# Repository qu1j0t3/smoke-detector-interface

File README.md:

# smoke-detector-interface
Interface board for Amphenol Telaire SM-UART-04L laser dust sensor, with some random other functions

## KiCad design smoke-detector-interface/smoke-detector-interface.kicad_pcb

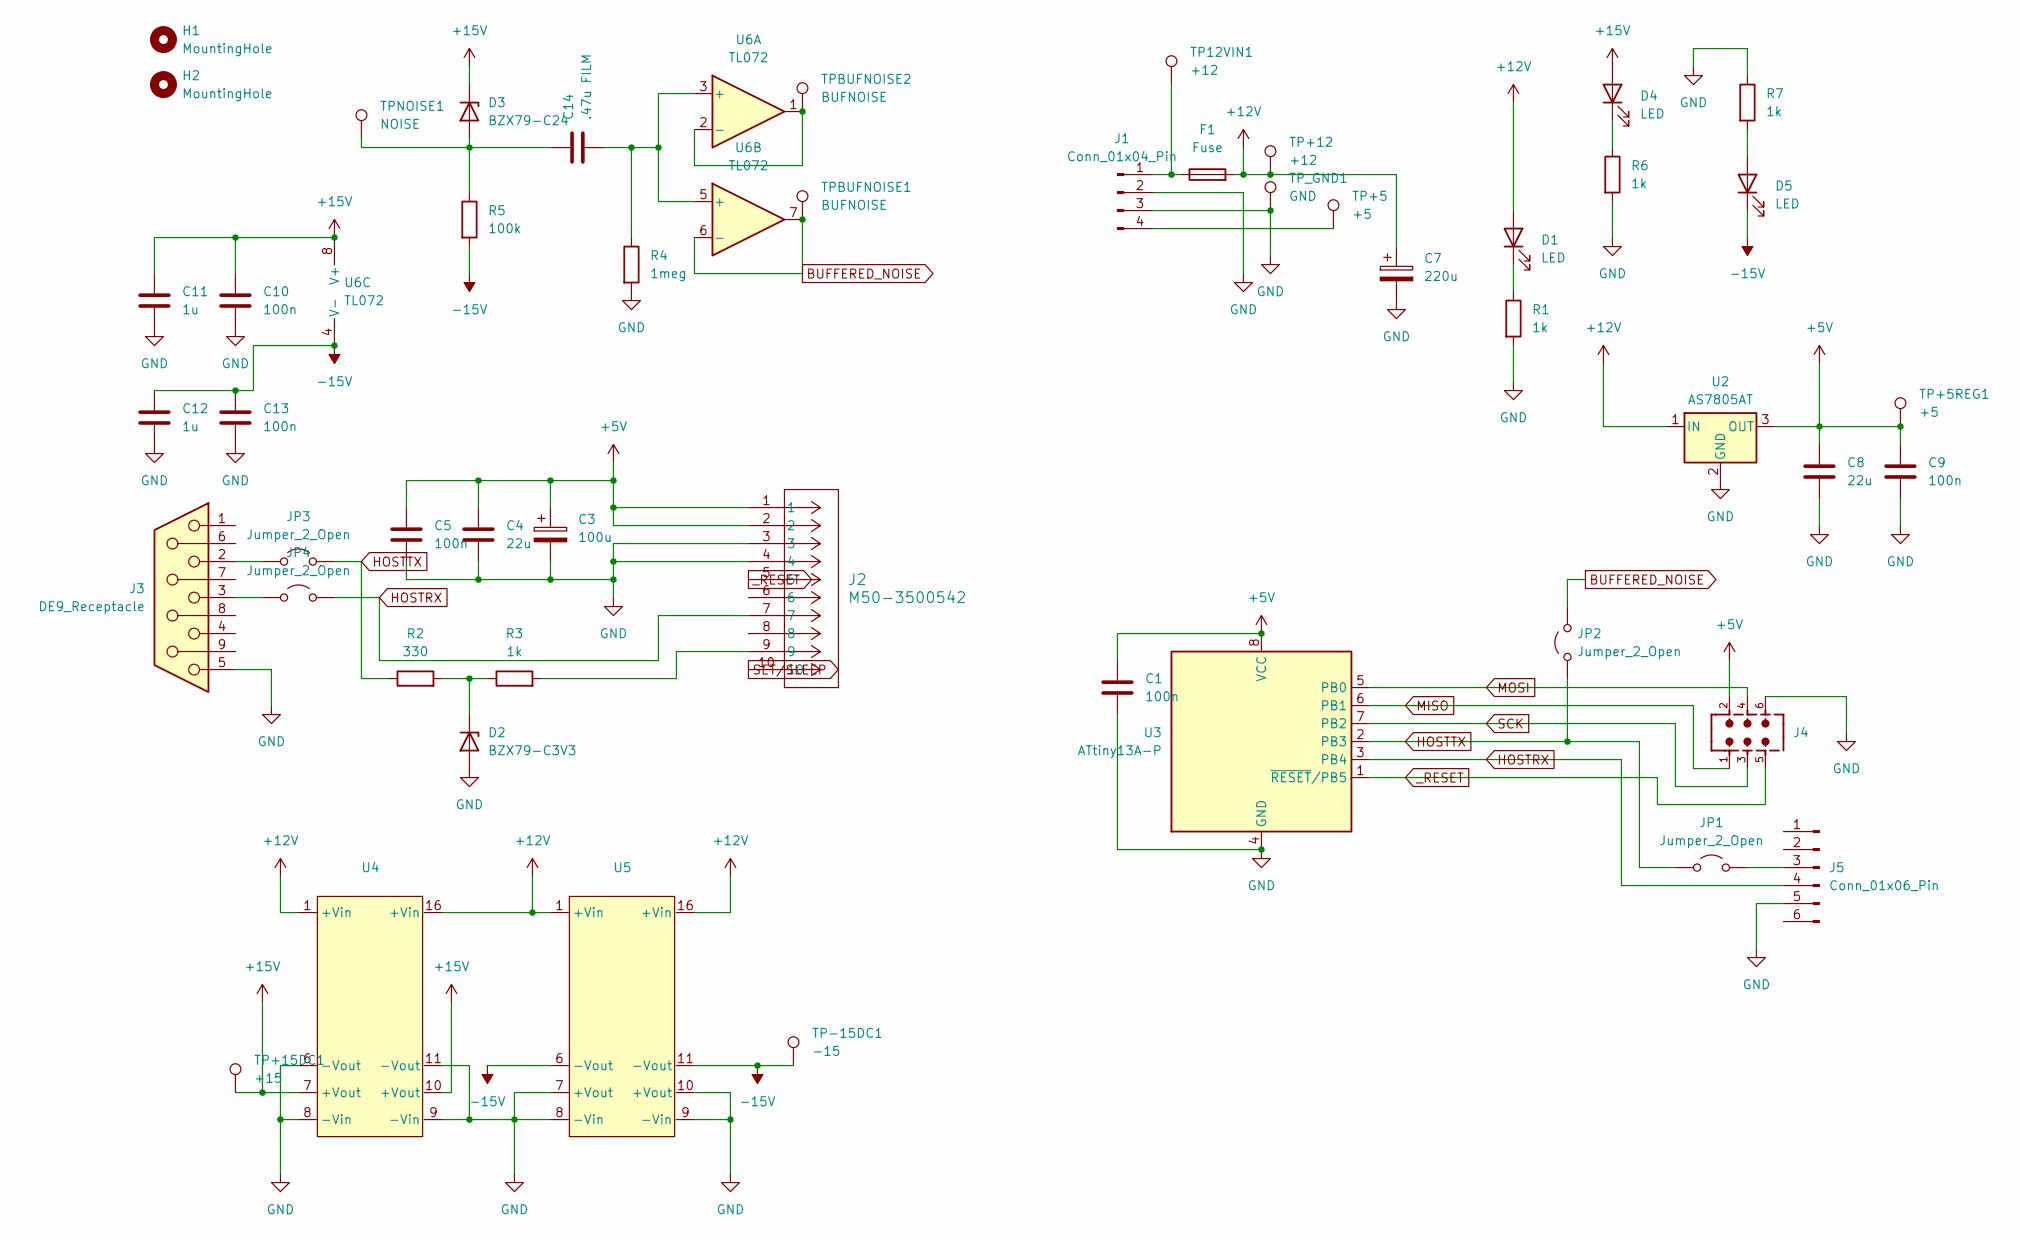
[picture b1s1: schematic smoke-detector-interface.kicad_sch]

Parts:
C1, C5, C9, C10, C13: 100n; C_Disc_D4.3mm_W1.9mm_P5.00mm
C3: 100u; CP_Radial_D6.3mm_P2.50mm
C4, C8: 22u; CP_Radial_D5.0mm_P2.00mm
C7: 220u; CP_Axial_L18.0mm_D8.0mm_P25.00mm_Horizontal
C11, C12: 1u; C_Disc_D3.8mm_W2.6mm_P2.50mm
C14: .47u FILM; C_Rect_L7.2mm_W3.5mm_P5.00mm_FKS2_FKP2_MKS2_MKP2
D1, D4, D5: LED; LED_D5.0mm
D2: BZX79-C3V3; D_DO-35_SOD27_P7.62mm_Horizontal
D3: BZX79-C24; D_DO-35_SOD27_P12.70mm_Horizontal
F1: Fuse; 01530008
H1, H2: MountingHole; MountingHole_3.2mm_M3
J1: Conn_01x04_Pin; 641737-1_TYC
J2: M50-3500542; CONN10_500542_HRW
J3: DE9_Receptacle; LD09S13A4GX00LF_AMP
J4: 61200621621; PART-NUMBER 61200621621
J5: Conn_01x06_Pin; PinHeader_1x06_P2.54mm_Vertical
JP1, JP2, JP3, JP4: Jumper_2_Open; R_Axial_DIN0204_L3.6mm_D1.6mm_P7.62mm_Horizontal
R1, R3, R6, R7: 1k; R_Axial_DIN0207_L6.3mm_D2.5mm_P10.16mm_Horizontal
R2: 330; R_Axial_DIN0207_L6.3mm_D2.5mm_P10.16mm_Horizontal
R4: 1meg; R_Axial_DIN0207_L6.3mm_D2.5mm_P10.16mm_Horizontal
R5: 100k; R_Axial_DIN0207_L6.3mm_D2.5mm_P10.16mm_Horizontal
TP12VIN1: +12; TestPoint_THTPad_2.5x2.5mm_Drill1.2mm
TP+5, TP+5REG1: +5; TestPoint_THTPad_2.5x2.5mm_Drill1.2mm
TP+12: +12; TestPoint_THTPad_2.5x2.5mm_Drill1.2mm
TP+15DC1: +15; TestPoint_THTPad_2.5x2.5mm_Drill1.2mm
TP-15DC1: -15; TestPoint_THTPad_2.5x2.5mm_Drill1.2mm
TPBUFNOISE1, TPBUFNOISE2: BUFNOISE; TestPoint_THTPad_2.5x2.5mm_Drill1.2mm
TPNOISE1: NOISE; TestPoint_THTPad_2.5x2.5mm_Drill1.2mm
TP_GND1: GND; TestPoint_THTPad_2.5x2.5mm_Drill1.2mm
U2: AS7805AT; TO-220-3_Vertical
U3: ATtiny13A-P; DIP-8_W7.62mm_Socket
U4, U5: DIP-16_W7.62mm_Socket
U6: TL072; DIP-8_W7.62mm_Socket

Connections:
+5V: C1.1, C3.1, C4.1, C5.1, C8.1, C9.1, J2.1, J2.2, J4.2, TP+5REG1.1, U2.3 (OUT), U3.8 (VCC)
+12V: C7.1, D1.2 (A), F1.2, TP+12.1, U2.1 (IN), U4.1 (+Vin), U4.16 (+Vin), U5.1 (+Vin), U5.16 (+Vin)
+15V: C10.1, C11.1, D3.1 (K), D4.2 (A), TP+15DC1.1, U4.7 (+Vout), U4.10 (+Vout), U6.8 (V+)
-15V: C12.1, C13.1, D5.1 (K), R5.2, TP-15DC1.1, U5.6 (-Vout), U5.11 (-Vout), U6.4 (V-)
BUFFERED_NOISE: JP2.2 (B), TPBUFNOISE1.1, U6.6 (-), U6.7
GND: C1.2, C3.2, C4.2, C5.2, C7.2, C8.2, C9.2, C10.2, C11.2, C12.2, C13.2, D2.2 (A), J1.2, J1.3, J2.3, J2.4, J3.5, J4.6, J5.5, R1.2, R4.2, R6.2, R7.1, TP_GND1.1, U2.2 (GND), U3.4 (GND), U4.6 (-Vout), U4.8 (-Vin), U4.9 (-Vin), U4.11 (-Vout), U5.7 (+Vout), U5.8 (-Vin), U5.9 (-Vin), U5.10 (+Vout)
HOSTRX: J2.7, J5.4, JP4.2 (B), U3.3 (PB4)
HOSTTX: JP1.1 (A), JP2.1 (A), JP3.2 (B), R2.1, U3.2 (PB3)
MISO: J4.1, U3.6 (PB1)
MOSI: J4.4, U3.5 (PB0)
unnamed: D1.1 (K), R1.1
unnamed: D2.1 (K), R2.2, R3.1
unnamed: C14.1, D3.2 (A), R5.1, TPNOISE1.1
unnamed: D4.1 (K), R6.1
unnamed: D5.2 (A), R7.2
unnamed: F1.1, J1.1, TP12VIN1.1
unnamed: J1.4, TP+5.1
unnamed: J2.9, R3.2
unnamed: J5.3, JP1.2 (B)
unnamed: J3.2, JP3.1 (A)
unnamed: J3.3, JP4.1 (A)
unnamed: C14.2, R4.1, U6.3 (+), U6.5 (+)
unnamed: TPBUFNOISE2.1, U6.1, U6.2 (-)
SCK: J4.3, U3.7 (PB2)
SET/SLEEP: J2.10
_RESET: J2.5, J4.5, U3.1 (~RESET/PB5)

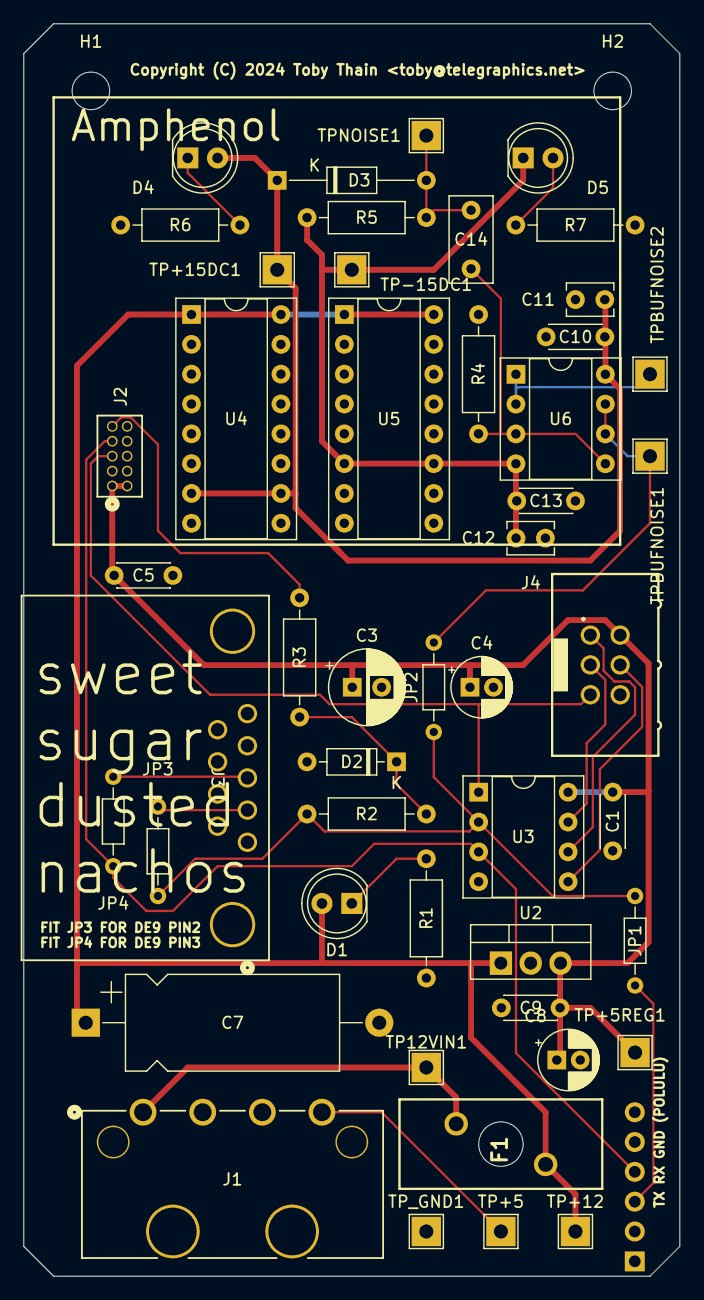
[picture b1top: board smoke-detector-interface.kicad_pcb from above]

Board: 2 copper layers, 55.9 x 106.7 mm, 51 parts (1 on the bottom side), 25 nets.

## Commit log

2024-08-18 Initial commit.
2024-08-18 Improved routing.
2024-08-19 Updates for Zenerglass parts.
2024-08-19 Add mounting holes.
2024-08-19 DRC passes.
2024-08-19 Add jumpers to serial rx/tx in case they need swapping.
2024-08-19 First production candidate.
2024-08-19 Add ignores.

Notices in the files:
smoke-detector-interface/smoke-detector-interface.kicad_pcb:
Copyright (C) 2024 Toby Thain
